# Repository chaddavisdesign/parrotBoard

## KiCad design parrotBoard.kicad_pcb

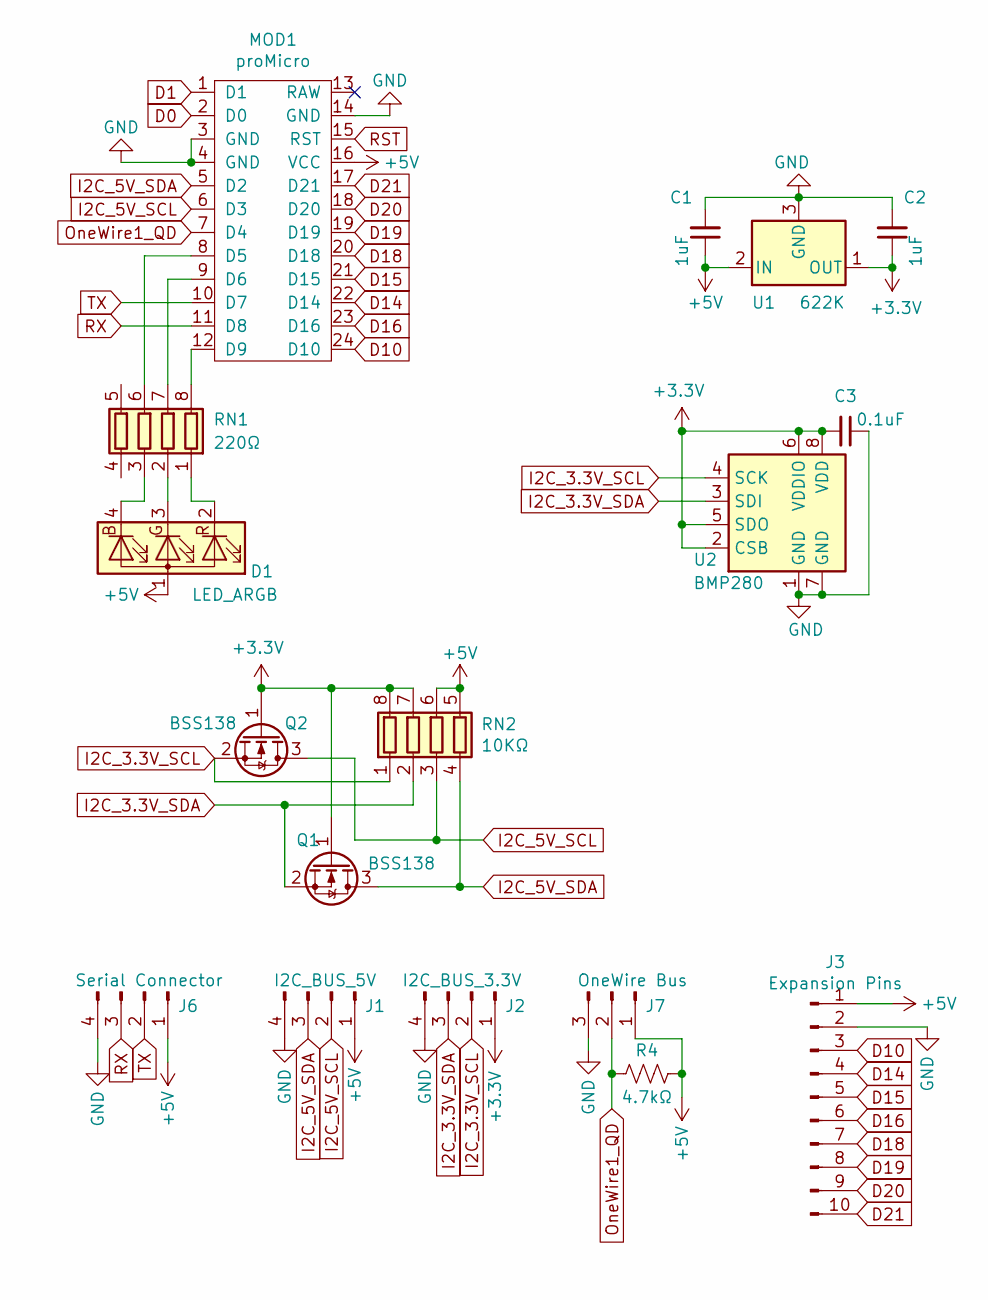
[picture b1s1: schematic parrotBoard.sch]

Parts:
C1, C2: 1uF; C_0603_1608Metric
C3: 0.1uF; C_0603_1608Metric
D1: LED_ARGB; LED_D5.0mm-4_RAGB
J1: I2C_BUS_5V; Molex_KK-254_AE-6410-04A_1x04_P2.54mm_Vertical
J2: I2C_BUS_3.3V; Molex_KK-254_AE-6410-04A_1x04_P2.54mm_Vertical
J3: Expansion Pins; PinHeader_1x10_P2.54mm_Vertical
J6: Serial Connector; Molex_KK-254_AE-6410-04A_1x04_P2.54mm_Vertical
J7: OneWire Bus; Molex_KK-254_AE-6410-03A_1x03_P2.54mm_Vertical
MOD1: proMicro; ProMicro
Q1, Q2: BSS138; SOT-23
R4: 4.7kΩ; R_0603_1608Metric
RN1: 220Ω; R_Array_Convex_4x0603
RN2: 10KΩ; R_Array_Convex_4x0603
U1: 622K; SOT-23
U2: BMP280; Bosch_LGA-8_2x2.5mm_P0.65mm_ClockwisePinNumbering

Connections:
+3V3: C2.1, C3.2, J2.1, Q1.1 (G), Q2.1 (G), RN2.7 (R2.2), RN2.8 (R1.2), U1.1 (OUT), U2.2 (CSB), U2.5 (SDO), U2.6 (VDDIO), U2.8 (VDD)
+5V: C1.1, D1.1 (A), J1.1, J3.1, J6.1, J7.1, MOD1.16 (VCC), R4.2, RN2.5 (R4.2), RN2.6 (R3.2), U1.2 (IN)
D10: J3.3, MOD1.24 (D10)
D14: J3.4, MOD1.22 (D14)
D15: J3.5, MOD1.21 (D15)
D16: J3.6, MOD1.23 (D16)
D18: J3.7, MOD1.20 (D18)
D19: J3.8, MOD1.19 (D19)
D20: J3.9, MOD1.18 (D20)
D21: J3.10, MOD1.17 (D21)
GND: C1.2, C2.2, C3.1, J1.4, J2.4, J3.2, J6.4, J7.3, MOD1.3 (GND), MOD1.4 (GND), MOD1.14 (GND), U1.3 (GND), U2.1 (GND), U2.7 (GND)
I2C_3.3V_SCL: J2.2, Q2.2 (S), RN2.1 (R1.1), U2.4 (SCK)
I2C_3.3V_SDA: J2.3, Q1.2 (S), RN2.2 (R2.1), U2.3 (SDI)
I2C_5V_SCL: J1.2, MOD1.6 (D3), Q2.3 (D), RN2.3 (R3.1)
I2C_5V_SDA: J1.3, MOD1.5 (D2), Q1.3 (D), RN2.4 (R4.1)
unnamed: D1.2 (RK), RN1.1 (R1.1)
unnamed: D1.3 (GK), RN1.2 (R2.1)
unnamed: D1.4 (BK), RN1.3 (R3.1)
unnamed: MOD1.8 (D5), RN1.6 (R3.2)
unnamed: MOD1.9 (D6), RN1.7 (R2.2)
unnamed: MOD1.12 (D9), RN1.8 (R1.2)
OneWire1_QD: J7.2, MOD1.7 (D4), R4.1
RX: J6.3, MOD1.11 (D8)
TX: J6.2, MOD1.10 (D7)

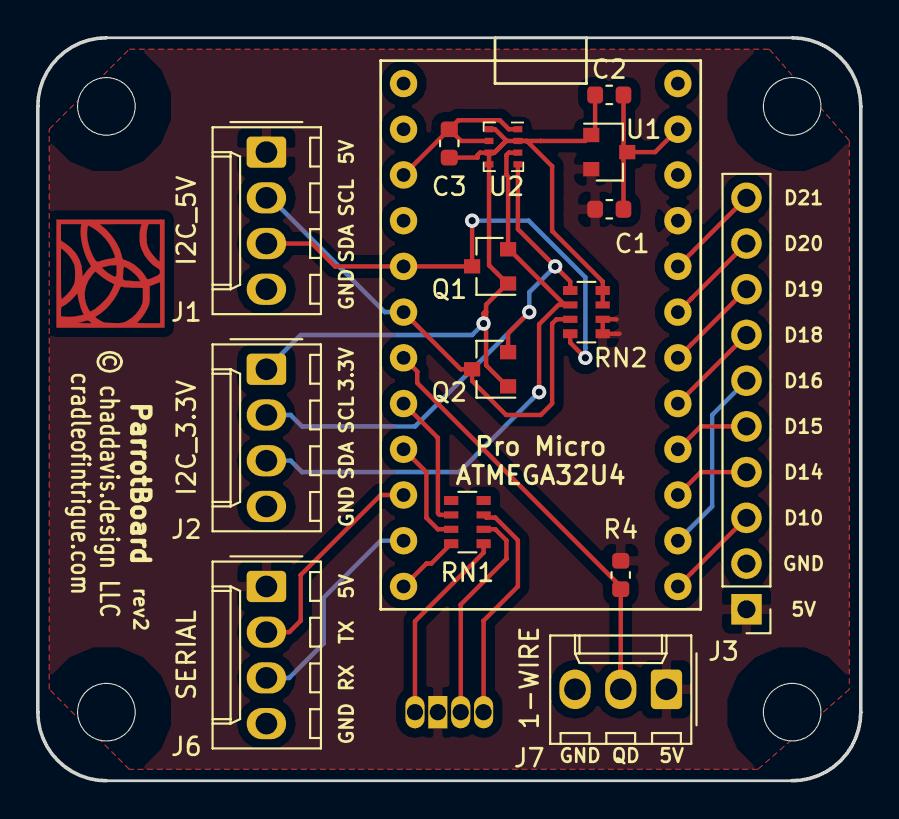
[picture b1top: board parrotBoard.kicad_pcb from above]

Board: 2 copper layers, 45.7 x 41.3 mm, 16 parts (1 on the bottom side), 11 nets.

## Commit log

2020-04-06 added gerber files

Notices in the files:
parrotBoard.kicad_pcb:
Licensed under CERN-OHL-S v2 https://cern.ch/cern-oh
©chaddavis.design, LLC 2020
